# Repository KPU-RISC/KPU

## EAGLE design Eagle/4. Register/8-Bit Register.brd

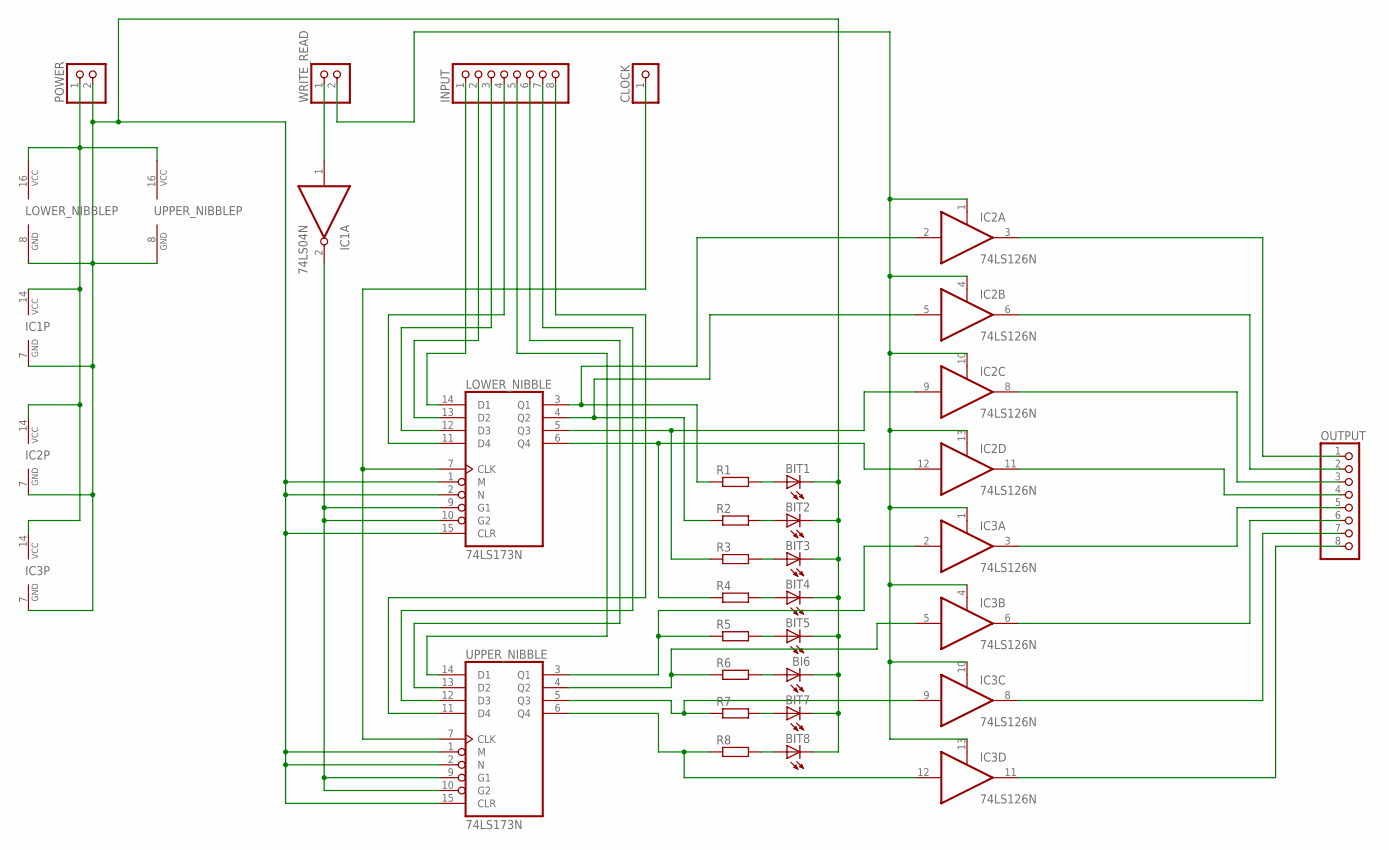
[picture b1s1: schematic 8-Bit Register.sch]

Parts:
BI6: LED3MM
BIT1, BIT2, BIT3, BIT4, BIT5, BIT7, BIT8: LED3MM
CLOCK: PINHD-1X1; 1X01
IC1: 74LS04N; DIL14
IC2, IC3: 74LS126N; DIL14
INPUT: PINHD-1X8; 1X08
LOWER_NIBBLE: 74LS173N; DIL16
OUTPUT: PINHD-1X8; 1X08
POWER: PINHD-1X2; 1X02
R1, R2, R3, R4, R5, R6, R7, R8: R-EU_0207/10; 0207/10
UPPER_NIBBLE: 74LS173N; DIL16
WRITE_READ: PINHD-1X2; 1X02

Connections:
GND: BI6.K (C), BIT1.K (C), BIT2.K (C), BIT3.K (C), BIT4.K (C), BIT5.K (C), BIT7.K (C), BIT8.K (C), IC1.7 (GND), IC2.7 (GND), IC3.7 (GND), LOWER_NIBBLE.1 (M), LOWER_NIBBLE.2 (N), LOWER_NIBBLE.8 (GND), LOWER_NIBBLE.15 (CLR), POWER.2, UPPER_NIBBLE.1 (M), UPPER_NIBBLE.2 (N), UPPER_NIBBLE.8 (GND), UPPER_NIBBLE.15 (CLR)
unnamed: BIT8.A, R8.2
unnamed: IC1.1 (I), WRITE_READ.1
unnamed: BIT1.A, R1.2
unnamed: BIT2.A, R2.2
unnamed: BIT3.A, R3.2
unnamed: BIT4.A, R4.2
unnamed: BIT5.A, R5.2
unnamed: BI6.A, R6.2
unnamed: BIT7.A, R7.2
unnamed: IC2.11 (O), OUTPUT.4
unnamed: IC1.2 (O), LOWER_NIBBLE.9 (G1), LOWER_NIBBLE.10 (G2), UPPER_NIBBLE.9 (G1), UPPER_NIBBLE.10 (G2)
unnamed: CLOCK.1, LOWER_NIBBLE.7 (CLK), UPPER_NIBBLE.7 (CLK)
unnamed: INPUT.1, LOWER_NIBBLE.14 (D1)
unnamed: INPUT.2, LOWER_NIBBLE.13 (D2)
unnamed: INPUT.3, LOWER_NIBBLE.12 (D3)
unnamed: INPUT.4, LOWER_NIBBLE.11 (D4)
unnamed: INPUT.6, UPPER_NIBBLE.13 (D2)
unnamed: INPUT.5, UPPER_NIBBLE.14 (D1)
unnamed: INPUT.7, UPPER_NIBBLE.12 (D3)
unnamed: INPUT.8, UPPER_NIBBLE.11 (D4)
unnamed: IC2.2 (I), LOWER_NIBBLE.3 (Q1), R1.1
unnamed: IC2.5 (I), LOWER_NIBBLE.4 (Q2), R2.1
unnamed: IC2.9 (I), LOWER_NIBBLE.5 (Q3), R3.1
unnamed: IC2.12 (I), LOWER_NIBBLE.6 (Q4), R4.1
unnamed: IC3.2 (I), R5.1, UPPER_NIBBLE.3 (Q1)
unnamed: IC3.5 (I), R6.1, UPPER_NIBBLE.4 (Q2)
unnamed: IC3.9 (I), R7.1, UPPER_NIBBLE.5 (Q3)
unnamed: IC3.12 (I), R8.1, UPPER_NIBBLE.6 (Q4)
unnamed: IC2.1 (OE), IC2.4 (OE), IC2.10 (OE), IC2.13 (OE), IC3.1 (OE), IC3.4 (OE), IC3.10 (OE), IC3.13 (OE), WRITE_READ.2
unnamed: IC2.3 (O), OUTPUT.1
unnamed: IC2.6 (O), OUTPUT.2
unnamed: IC2.8 (O), OUTPUT.3
unnamed: IC3.3 (O), OUTPUT.5
unnamed: IC3.6 (O), OUTPUT.6
unnamed: IC3.8 (O), OUTPUT.7
unnamed: IC3.11 (O), OUTPUT.8
VCC: IC1.14 (VCC), IC2.14 (VCC), IC3.14 (VCC), LOWER_NIBBLE.16 (VCC), POWER.1, UPPER_NIBBLE.16 (VCC)

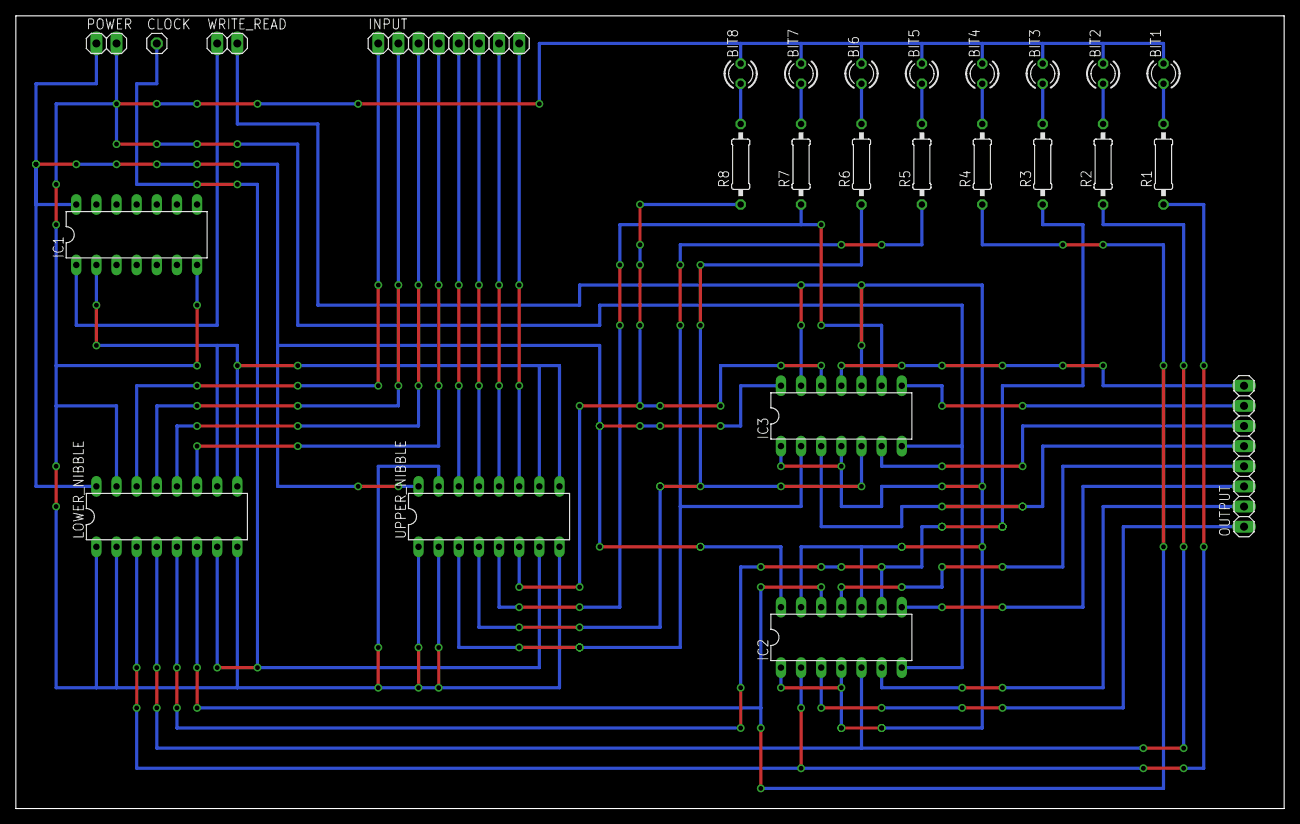
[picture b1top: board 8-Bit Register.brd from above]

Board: 2 copper layers, 160.0 x 100.0 mm, 26 parts (0 on the bottom side), 38 nets.

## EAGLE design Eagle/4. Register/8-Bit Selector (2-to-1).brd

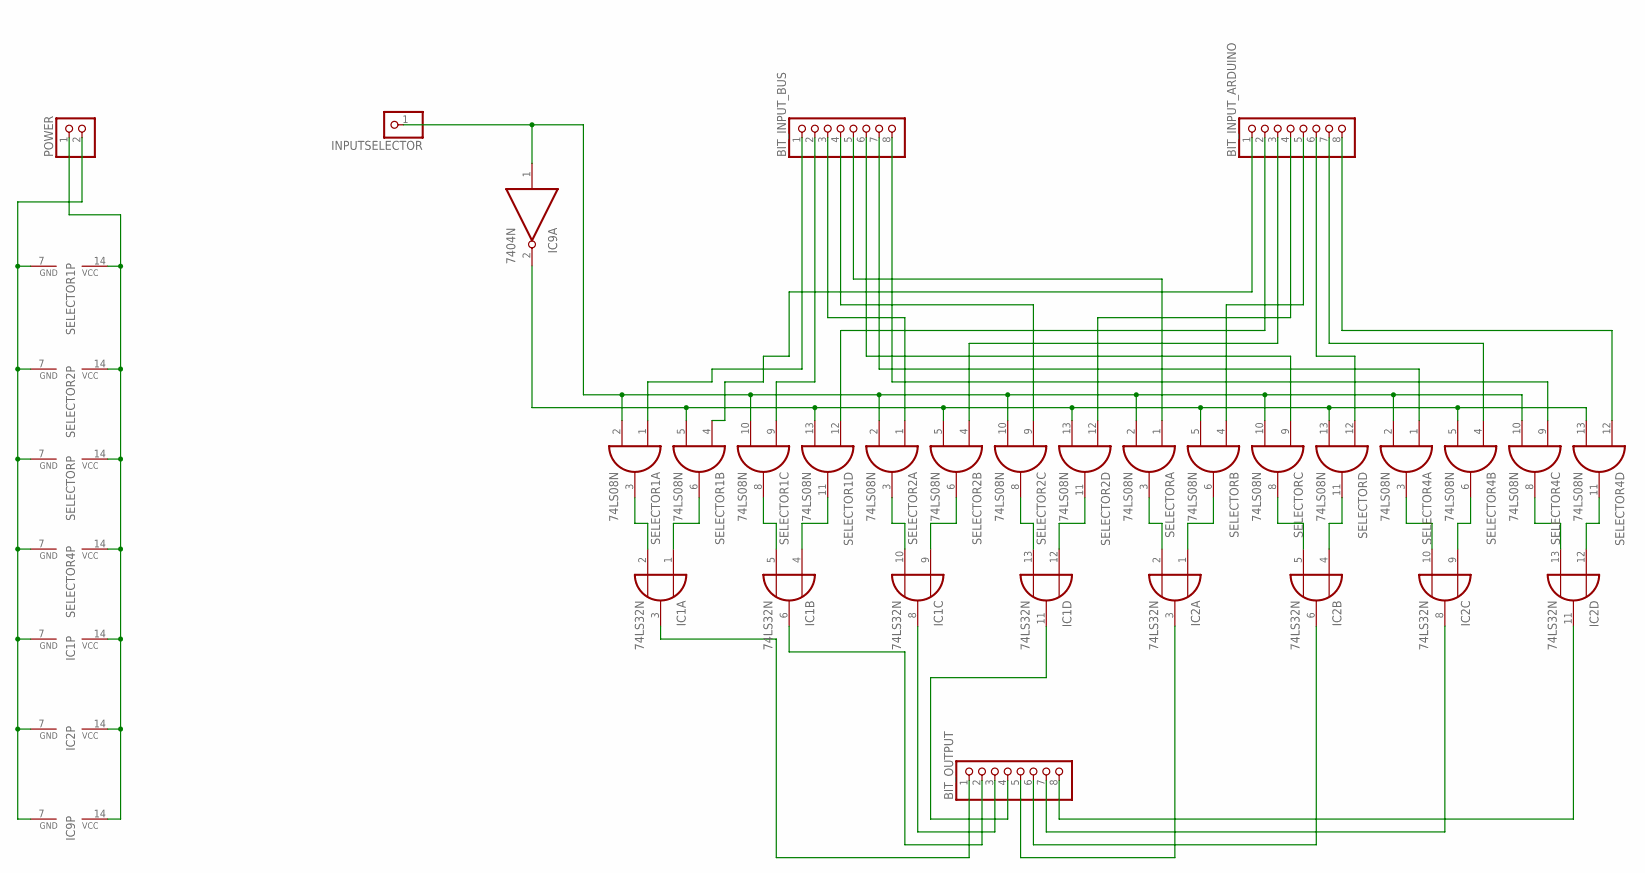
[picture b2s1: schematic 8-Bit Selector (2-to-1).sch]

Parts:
BIT_INPUT_ARDUINO: PINHD-1X8; 1X08
BIT_INPUT_BUS: PINHD-1X8; 1X08
BIT_OUTPUT: PINHD-1X8; 1X08
IC1, IC2: 74LS32N; DIL14
IC9: 7404N; DIL14
INPUTSELECTOR: PINHD-1X1; 1X01
POWER: PINHD-1X2; 1X02
SELECTOR, SELECTOR1, SELECTOR2, SELECTOR4: 74LS08N; DIL14

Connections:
GND: IC1.7 (GND), IC2.7 (GND), IC9.7 (GND), POWER.2, SELECTOR.7 (GND), SELECTOR1.7 (GND), SELECTOR2.7 (GND), SELECTOR4.7 (GND)
unnamed: IC9.1 (I), INPUTSELECTOR.1, SELECTOR.2 (I1), SELECTOR.10 (I1), SELECTOR1.2 (I1), SELECTOR1.10 (I1), SELECTOR2.2 (I1), SELECTOR2.10 (I1), SELECTOR4.2 (I1), SELECTOR4.10 (I1)
unnamed: IC9.2 (O), SELECTOR.5 (I1), SELECTOR.13 (I1), SELECTOR1.5 (I1), SELECTOR1.13 (I1), SELECTOR2.5 (I1), SELECTOR2.13 (I1), SELECTOR4.5 (I1), SELECTOR4.13 (I1)
unnamed: BIT_INPUT_BUS.1, SELECTOR1.1 (I0)
unnamed: BIT_INPUT_ARDUINO.1, SELECTOR1.4 (I0)
unnamed: BIT_INPUT_BUS.2, SELECTOR1.9 (I0)
unnamed: BIT_INPUT_ARDUINO.2, SELECTOR1.12 (I0)
unnamed: BIT_INPUT_BUS.3, SELECTOR2.1 (I0)
unnamed: BIT_INPUT_ARDUINO.3, SELECTOR2.4 (I0)
unnamed: BIT_INPUT_BUS.4, SELECTOR2.9 (I0)
unnamed: BIT_INPUT_ARDUINO.4, SELECTOR2.12 (I0)
unnamed: BIT_INPUT_BUS.5, SELECTOR.1 (I0)
unnamed: BIT_INPUT_ARDUINO.5, SELECTOR.4 (I0)
unnamed: BIT_INPUT_BUS.6, SELECTOR.9 (I0)
unnamed: BIT_INPUT_ARDUINO.6, SELECTOR.12 (I0)
unnamed: BIT_INPUT_BUS.7, SELECTOR4.1 (I0)
unnamed: BIT_INPUT_ARDUINO.7, SELECTOR4.4 (I0)
unnamed: BIT_INPUT_BUS.8, SELECTOR4.9 (I0)
unnamed: BIT_INPUT_ARDUINO.8, SELECTOR4.12 (I0)
unnamed: BIT_OUTPUT.6, IC2.6 (O)
unnamed: IC1.2 (I1), SELECTOR1.3 (O)
unnamed: IC1.1 (I0), SELECTOR1.6 (O)
unnamed: IC1.5 (I1), SELECTOR1.8 (O)
unnamed: IC1.4 (I0), SELECTOR1.11 (O)
unnamed: IC1.10 (I1), SELECTOR2.3 (O)
unnamed: IC1.9 (I0), SELECTOR2.6 (O)
unnamed: IC1.13 (I1), SELECTOR2.8 (O)
unnamed: IC1.12 (I0), SELECTOR2.11 (O)
unnamed: IC2.2 (I1), SELECTOR.3 (O)
unnamed: IC2.1 (I0), SELECTOR.6 (O)
unnamed: IC2.5 (I1), SELECTOR.8 (O)
unnamed: IC2.4 (I0), SELECTOR.11 (O)
unnamed: IC2.10 (I1), SELECTOR4.3 (O)
unnamed: IC2.9 (I0), SELECTOR4.6 (O)
unnamed: IC2.13 (I1), SELECTOR4.8 (O)
unnamed: IC2.12 (I0), SELECTOR4.11 (O)
unnamed: BIT_OUTPUT.1, IC1.3 (O)
unnamed: BIT_OUTPUT.2, IC1.6 (O)
unnamed: BIT_OUTPUT.3, IC1.8 (O)
unnamed: BIT_OUTPUT.4, IC1.11 (O)
unnamed: BIT_OUTPUT.5, IC2.3 (O)
unnamed: BIT_OUTPUT.7, IC2.8 (O)
unnamed: BIT_OUTPUT.8, IC2.11 (O)
VCC: IC1.14 (VCC), IC2.14 (VCC), IC9.14 (VCC), POWER.1, SELECTOR.14 (VCC), SELECTOR1.14 (VCC), SELECTOR2.14 (VCC), SELECTOR4.14 (VCC)

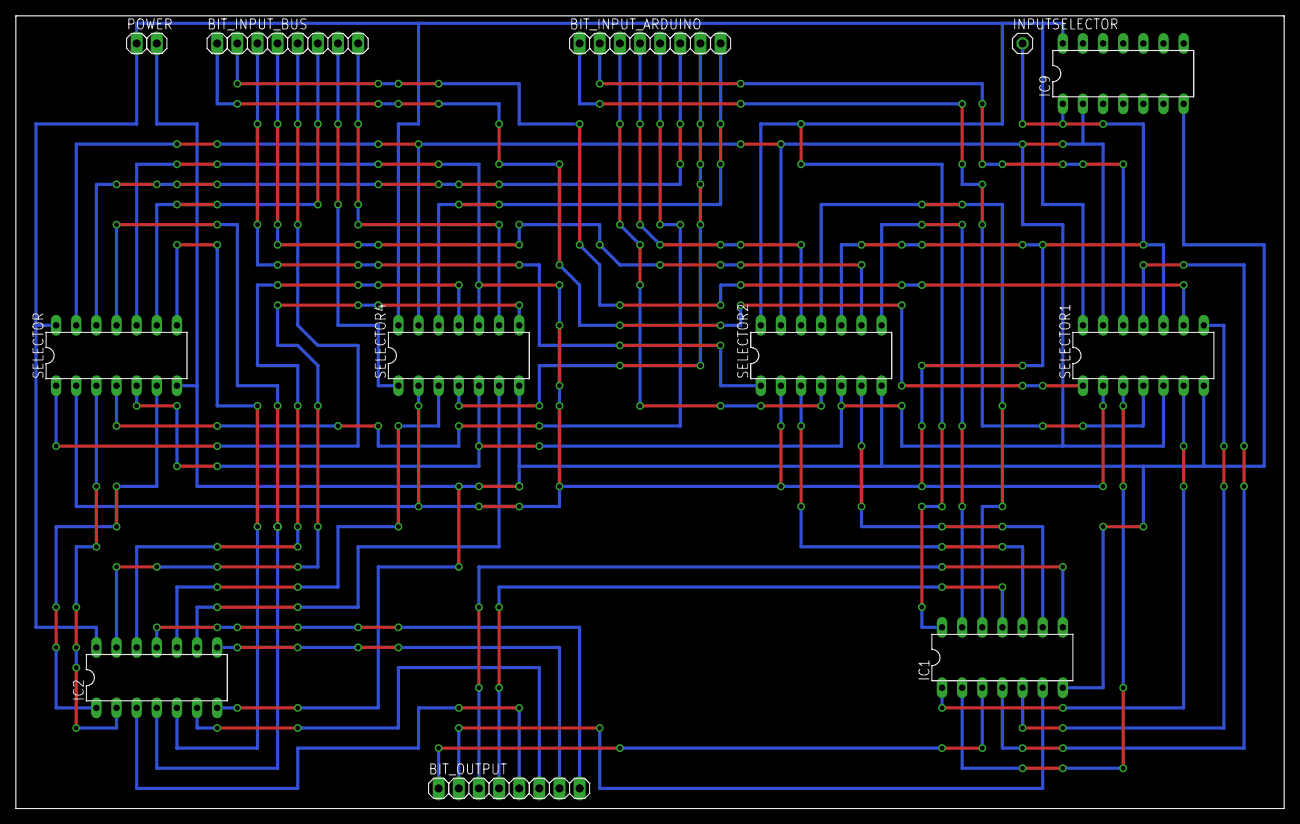
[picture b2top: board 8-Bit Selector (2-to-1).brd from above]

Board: 2 copper layers, 160.0 x 100.0 mm, 12 parts (0 on the bottom side), 44 nets.
